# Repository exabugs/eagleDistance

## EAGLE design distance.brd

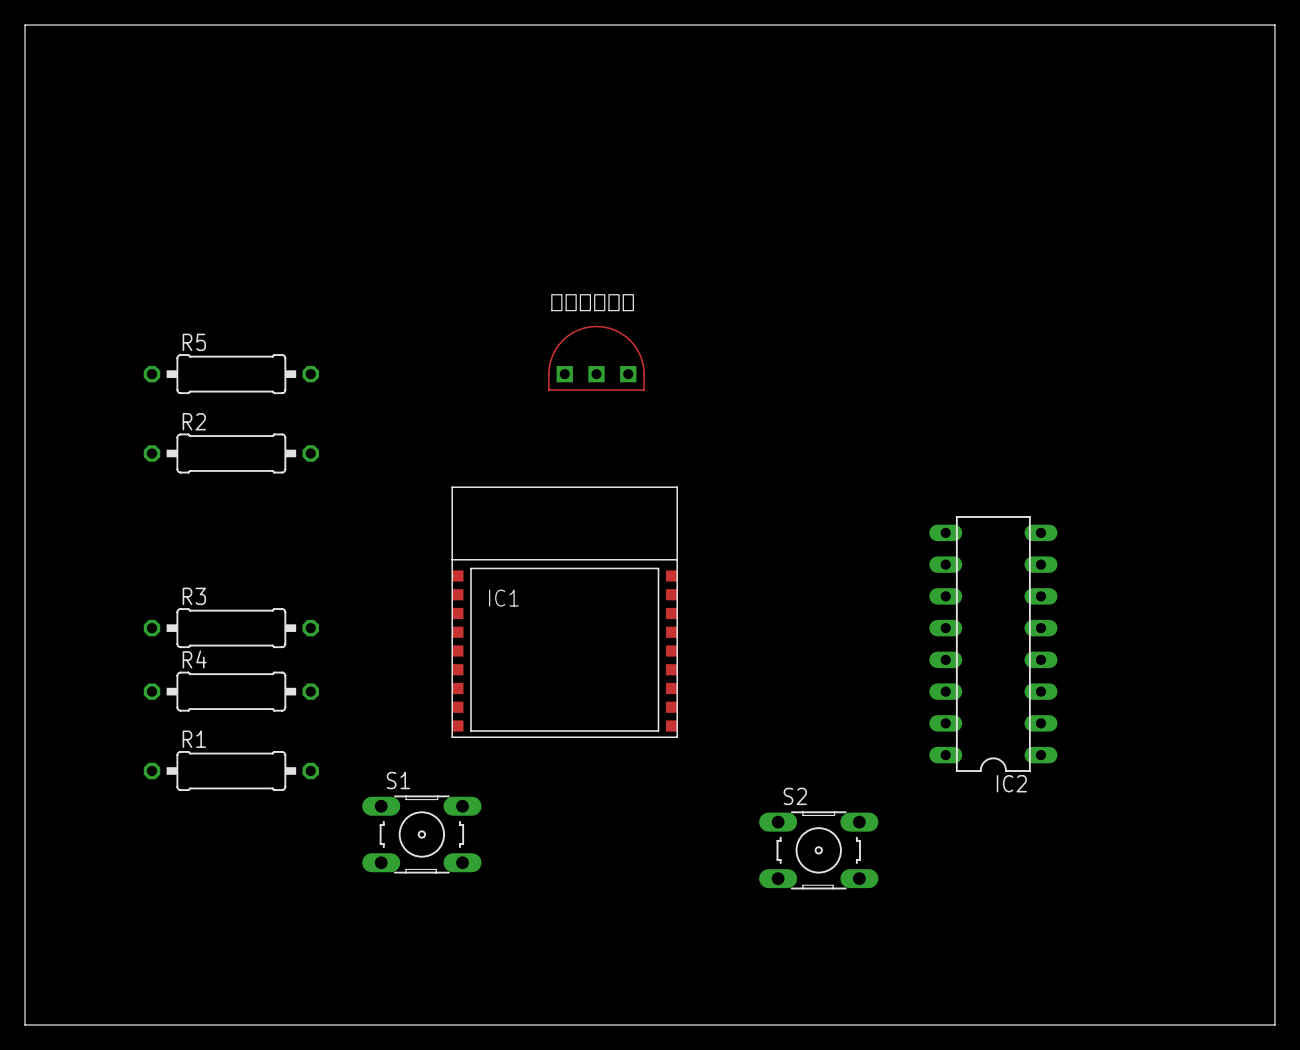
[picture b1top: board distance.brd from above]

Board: 2 copper layers, 100.0 x 80.0 mm, 10 parts (0 on the bottom side), 11 nets, no tracks yet.

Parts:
IC1: ESP-WROOM-02; WROOM-02
IC2: MCP3008; DIL16
R1, R2, R3, R4, R5: 10k; 0309/12
S1, S2: B3F-10XX
温度センサー: LM35

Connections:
+3.3V: IC1.1, IC2.15, IC2.16, R2.1, R3.1, R4.1, R5.2, 温度センサー.P$1
GND: IC1.9, IC1.13, IC1.18, IC2.5, IC2.6, IC2.7, IC2.8, IC2.9, IC2.14, R1.1, S1.1, S2.3, 温度センサー.P$3
unnamed: IC1.6, IC2.10, R1.2
unnamed: IC1.5, IC2.11
unnamed: IC1.4, IC2.12
unnamed: IC1.15, IC1.17, R4.2, S2.1
unnamed: IC1.7, R2.2
unnamed: IC1.3, IC2.13
unnamed: IC1.8, R3.2, S1.3
unnamed: IC2.1, 温度センサー.P$2
unnamed: IC1.2, R5.1

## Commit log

2016-01-17 First Commit.
